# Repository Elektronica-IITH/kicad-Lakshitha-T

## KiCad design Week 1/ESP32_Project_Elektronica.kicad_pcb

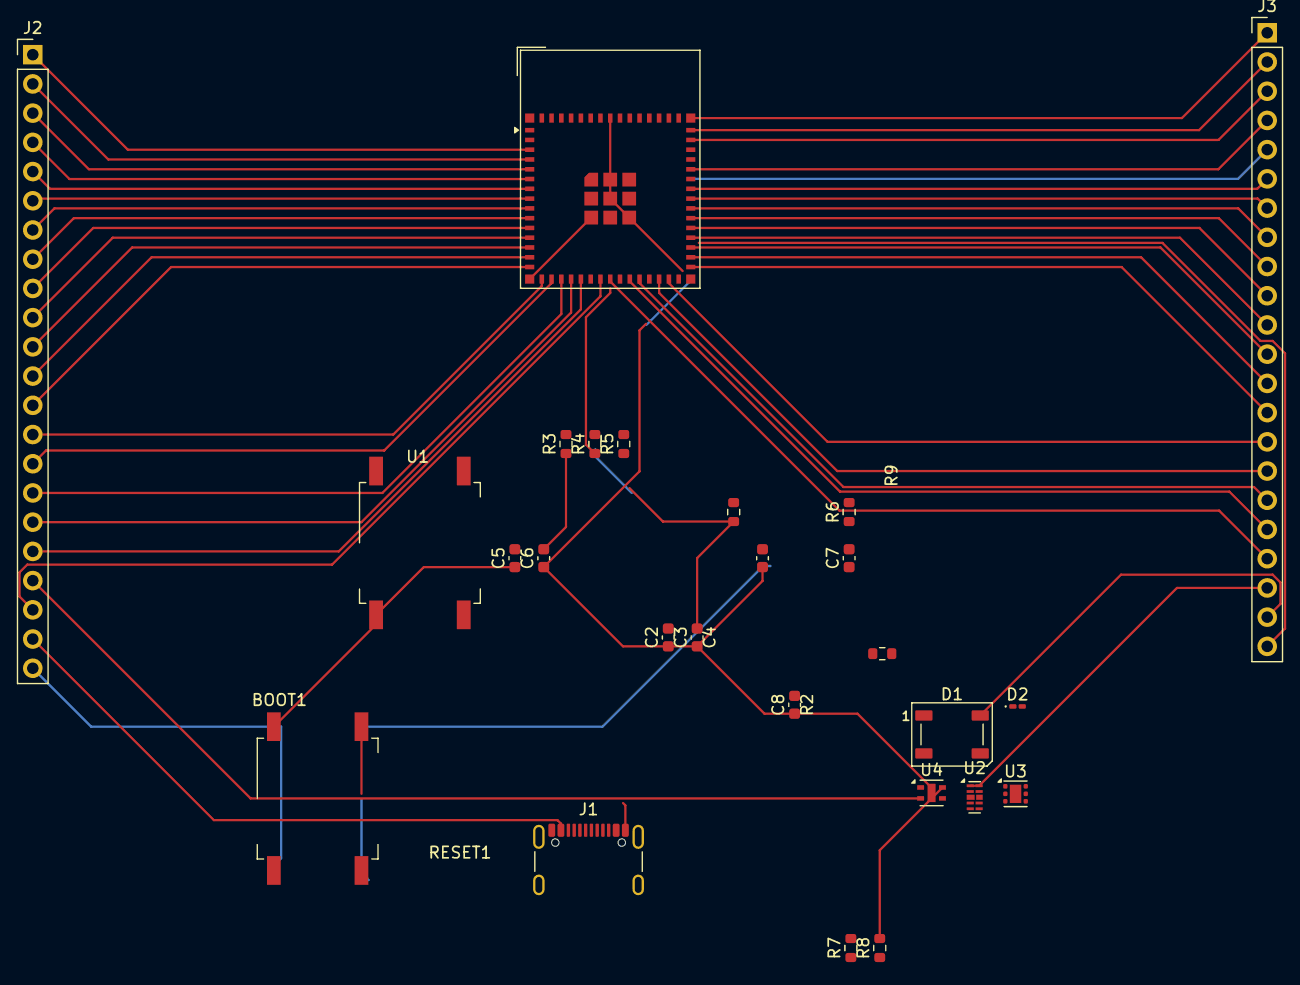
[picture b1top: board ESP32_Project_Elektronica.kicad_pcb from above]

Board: 2 copper layers, 26 parts (0 on the bottom side), 48 nets.

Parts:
BOOT1: SW_MEC_5GSH9
C2, C3, C4, C5, C6, C7, C8: C_0603_1608Metric
D1: WS2812B; LED_WS2812B_PLCC4_5.0x5.0mm_P3.2mm
D2: LED; LED_0201_0603Metric_Pad0.64x0.40mm_HandSolder
J1: USB_C_Receptacle_USB2.0_16P; USB_C_Receptacle_GCT_USB4105-xx-A_16P_TopMnt_Horizontal
J2, J3: Conn_01x22_Pin; PinHeader_1x22_P2.54mm_Vertical
R2, R3, R4, R5, R6, R7, R8, R9: R_0603_1608Metric
RESET1: SW_MEC_5GSH9
U1: ESP32-S3-MINI-1; ESP32-S2-MINI-1
U2: D3V3XA4B10LP; Diodes_UDFN-10_1.0x2.5mm_P0.5mm
U3: TLV75801PDRV; WSON-6-1EP_2x2mm_P0.65mm_EP1x1.6mm
U4: ENS210; AMS_QFN-4-1EP_2x2mm_P0.95mm_EP0.7x1.6mm

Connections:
/3V3: C2.2, C3.2, C6.2, C8.2, D1.1 (VDD), J2.1, R2.1, R3.1, R4.1, R7.1, R9.1, U1.3 (3V3), U3.1 (OUT), U4.1 (VDD)
/5VUSB: C7.2, J1.A4 (VBUS), J1.A9 (VBUS), J1.B4 (VBUS), J1.B9 (VBUS), J2.21, U2.4, U2.7 (NC), U3.4 (EN), U3.6 (IN)
/12C_SCL: J2.19, U4.2 (SCL)
/12C_SDA: J2.20, R2.2, U1.22 (IO18), U4.3 (SDA)
/ESP32_EN: C5.2, J3.2, R4.2, RESET1.3 (K), RESET1.4 (A), U1.45 (EN)
/GPIO0: BOOT1.3 (K), BOOT1.4 (A), C4.2, J2.2, U1.4 (IO0)
/GPIO1: J2.3, U1.5 (IO1)
/GPIO2: J2.4, U1.6 (IO2)
/GPIO3: J2.5, U1.7 (IO3)
/GPIO4: J2.6, U1.8 (IO4)
/GPIO5: J2.7, U1.9 (IO5)
/GPIO6: J2.8, U1.10 (IO6)
/GPIO7: J2.9, U1.11 (IO7)
/GPIO8: J2.10, U1.12 (IO8)
/GPIO9: J2.11, U1.13 (IO9)
/GPIO10: J2.12, U1.14 (IO10)
/GPIO11: J2.13, U1.15 (IO11)
/GPIO12: J2.14, U1.16 (IO12)
/GPIO13: J2.15, U1.17 (IO13)
/GPIO14: J2.16, U1.18 (IO14)
/GPIO15: J2.17, U1.19 (IO15)
/GPIO16: J2.18, U1.20 (IO16)
/GPIO21: J3.18, U1.25 (IO21)
/GPIO26: J3.17, U1.26 (IO26)
/GPIO33: J3.16, U1.28 (IO33)
/GPIO34: J3.15, U1.29 (IO34)
/GPIO35: J3.14, U1.31 (IO35)
/GPIO36: J3.13, U1.32 (IO36)
/GPIO37: J3.12, U1.33 (IO37)
/GPIO38: J3.11, U1.34 (IO38)
/GPIO39: J3.10, U1.35 (IO39)
/GPIO40: J3.9, U1.36 (IO40)
/GPIO41: J3.8, U1.37 (IO41)
/GPIO42: J3.7, U1.38 (IO42)
/GPIO45: J3.4, U1.41 (IO45)
/GPIO46: J3.3, U1.44 (IO46)
/GPIO47: J3.22, U1.27 (IO47)
/GPIO48: D1.4 (DIN), J3.21, U1.30 (IO48)
/RXD: J3.5, U1.40 (RXD0)
/TXD: J3.6, U1.39 (TXD0)
/USB_N: J1.A7 (D-), J1.B7 (D-), J3.19, U1.23 (USB_D-), U2.2, U2.9 (NC)
/USB_P: J1.A6 (D+), J1.B6 (D+), J3.20, U1.24 (USB_D+), U2.1, U2.10 (NC)
GND: BOOT1.1, BOOT1.2, C2.1, C3.1, C4.1, C5.1, C6.1, C7.1, C8.1, D1.3 (VSS), D2.1 (K), J1.A1 (GND), J1.A12 (GND), J1.B1 (GND), J1.B12 (GND), J1.S1 (SHIELD), J2.22, J3.1, R5.2, R6.2, R8.2, RESET1.1, RESET1.2, U1.1 (GND), U1.2 (GND), U1.42 (GND), U1.43 (GND), U1.46 (GND), U1.47 (GND), U1.48 (GND), U1.49 (GND), U1.50 (GND), U1.51 (GND), U1.52 (GND), U1.53 (GND), U1.54 (GND), U1.55 (GND), U1.56 (GND), U1.57 (GND), U1.58 (GND), U1.59 (GND), U1.60 (GND), U1.61 (GND), U1.62 (GND), U1.63 (GND), U1.64 (GND), U1.65 (GND), U2.3 (VSS), U2.8 (VSS), U3.3 (GND), U3.7 (GND), U4.4 (GND), U4.5 (GND)
unnamed: D2.2 (A), R9.2
unnamed: J1.A5 (CC1), R5.1
unnamed: J1.B5 (CC2), R6.1
unnamed: R3.2, U1.21 (IO17)
unnamed: R7.2, R8.1, U3.2 (FB)

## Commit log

2025-03-30 Automated PCB Check: Score 98/100
